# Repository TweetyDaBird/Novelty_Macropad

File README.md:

# Novelty_Macropad
 F*ckYou Macropad with 10 keys (ISO Enter, 2.75u Space, 7 pcs 1u + 1 pcs 1u/1.25u Shift)
 
 Inspired by this Reddit thread https://www.reddit.com/r/MechanicalKeyboards/comments/kn0asz/dont_let_your_memes_be_dreams/
 
 * Sub 100x100mm PCB for low cost fabrication
 * Easily soldereable for novice with simple components
 * 10 Cherry MX compatible Kaihl Hot-Swap sockets (with alternate 1u/1.25u layout for shift key)
 * Supports platemounted Cherry style stabilizers
 * Can be used with a ProMicro/EliteC connected to pinheader, or by soldering onboard SMD Atmega32u4 and associated components
 * If used with SMD components, USB-C port (USB2.0)
 * Includes .STEP file of PCB and plate holes for case design
 
 If anyone designs a nice design for a CNC machined or 3D printed case, please let me know (pull), and I'll include the files in the Github.

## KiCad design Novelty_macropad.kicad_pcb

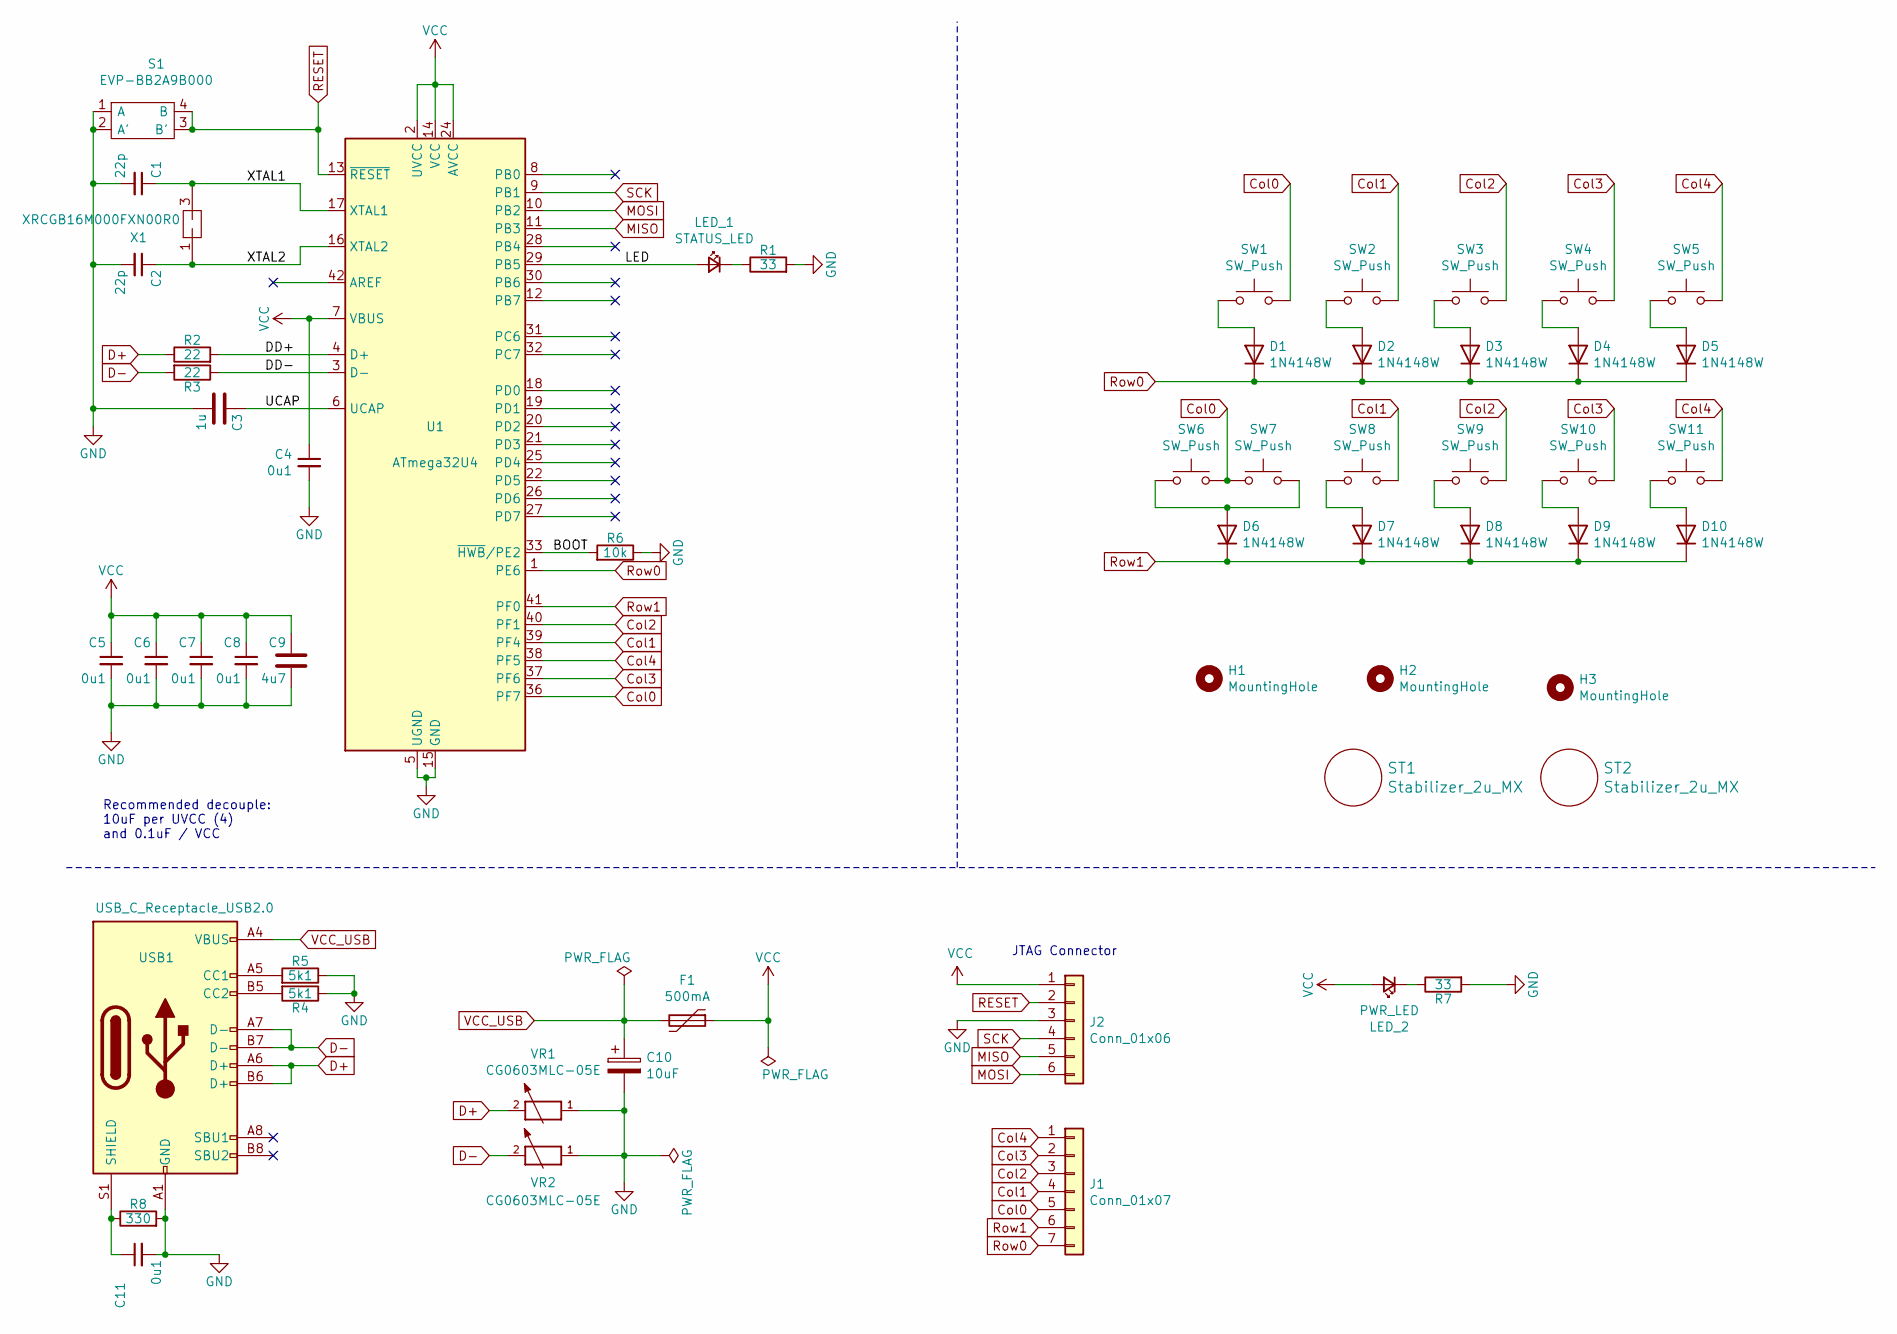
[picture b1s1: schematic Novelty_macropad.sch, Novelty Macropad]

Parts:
C1, C2: 22p; C_0603_1608Metric; Manufacturer_Part_Number 06035A220JAT2A; Mouser Part Number 581-06035A220J
C3: 1u; C_0805_2012Metric; Manufacturer_Part_Number CL21B105KBFNNNG; Mouser Part Number 187-CL21B105KBFNNNG
C4, C5, C6, C7, C8, C11: 0u1; C_0603_1608Metric; Manufacturer_Part_Number 06035C104JAT2A; Mouser Part Number 581-06035C104JAT2A
C9: 4u7; C_0805_2012Metric; Manufacturer_Part_Number C2012X7R1H475K125AC; Mouser Part Number 810-C2012X7R475K125C
C10: 10uF; CP_EIA-3216-18_Kemet-A; Manufacturer_Part_Number TAJA106M010RNJ; Mouser Part Number 581-TAJA106M010R
D1, D2, D3, D4, D5, D6, D7, D8, D9, D10: 1N4148W; Diode_DO35_SOD123
F1: 500mA; Fuse_0603_1608Metric; Manufacturer_Part_Number 04000025WR; Mouser Part Number 576-04000025WR
H1, H2, H3: MountingHole; MountingHole_2.7mm_M2.5
J1: Conn_01x07; PinHeader_1x07_P2.54mm_Vertical
J2: Conn_01x06; PinHeader_2x03_P2.54mm_Vertical; Manufacturer_Part_Number Pinheader
LED_1: STATUS_LED; LED_0603_1608Metric; Manufacturer_Part_Number APT1608EC; Mouser Part Number 604-APT1608EC
LED_2: PWR_LED; LED_0603_1608Metric; Manufacturer_Part_Number APT1608EC; Mouser Part Number 604-APT1608EC
R1, R7: 33; R_0603_1608Metric; Manufacturer_Part_Number ERJ-3EKF33R0V; Mouser Part Number 667-ERJ-3EKF33R0V
R2, R3: 22; R_0603_1608Metric; Manufacturer_Part_Number ERJ-3GEYJ220V; Mouser Part Number 667-ERJ-3GEYJ220V
R4, R5: 5k1; R_0603_1608Metric; Manufacturer_Part_Number ERJ-3EKF5101V; Mouser Part Number 667-ERJ-3EKF5101V
R6: 10k; R_0603_1608Metric; Manufacturer_Part_Number ERJ-3EKF1002V; Mouser Part Number 667-ERJ-3GEYJ103V
R8: 330; R_0603_1608Metric; Manufacturer_Part_Number ERJ-3EKF3300V; Mouser Part Number 667-ERJ-3EKF3300V
S1: EVP-BB2A9B000; EVPBB2A9B000; Mouser Part Number 667-EVP-BB2A9B000
ST1, ST2: Stabilizer_2u_MX; Stabilizer_MX_2u
SW1, SW2, SW3, SW4, SW5, SW6, SW7, SW8, SW9, SW10, SW11: SW_Push; Kailh_socket_MX
U1: ATmega32U4; QFN-44-1EP_7x7mm_P0.5mm_EP5.15x5.15mm_ThermalVias; Manufacturer_Part_Number ATMEGA32U4RC-MU; Mouser Part Number 556-ATMEGA32U4RC-MU
USB1: USB_C_Receptacle_USB2.0; HRO-TYPE-C-31-M-12-Assembly; Manufacturer_Part_Number HRO-TYPE-C-31-M-14
VR1, VR2: CG0603MLC-05E; R_0603_1608Metric; Mouser Part Number 652-CG0603MLC-05E
X1: XRCGB16M000FXN00R0; XRCGB16M000FXN1R0; Mouser Part Number 81-XRCGB16M000FXN00R

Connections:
/BOOT: R6.2, U1.33 (~HWB~/PE2)
/DD+: R2.2, U1.4 (D+)
/DD-: R3.1, U1.3 (D-)
/LED: LED_1.2 (A), U1.29 (PB5)
/UCAP: C3.1, U1.6 (UCAP)
/XTAL1: C1.1, U1.17 (XTAL1), X1.3
/XTAL2: C2.1, U1.16 (XTAL2), X1.1
Col0: J1.5, SW1.1, SW6.1, SW7.1, U1.36 (PF7)
Col1: J1.4, SW2.1, SW8.1, U1.39 (PF4)
Col2: J1.3, SW3.1, SW9.1, U1.40 (PF1)
Col3: J1.2, SW4.1, SW10.1, U1.37 (PF6)
Col4: J1.1, SW5.1, SW11.1, U1.38 (PF5)
D+: R2.1, USB1.A6 (D+), USB1.B6 (D+), VR1.2
D-: R3.2, USB1.A7 (D-), USB1.B7 (D-), VR2.2
GND: C1.2, C2.2, C3.2, C4.2, C5.2, C6.2, C7.2, C8.2, C9.2, C10.2, C11.2, J2.3, R1.2, R4.1, R5.1, R6.1, R7.2, R8.2, S1.1 (A), S1.2 (A'), U1.5 (UGND), U1.15 (GND), U1.23 (GND), U1.35 (GND), U1.43 (GND), USB1.A1 (GND), USB1.A12 (GND), USB1.B1 (GND), USB1.B12 (GND), VR1.1, VR2.1
MISO: J2.5, U1.11 (PB3)
MOSI: J2.6, U1.10 (PB2)
unnamed: C11.1, R8.1, USB1.S1 (SHIELD)
unnamed: D1.2 (A), SW1.2
unnamed: D2.2 (A), SW2.2
unnamed: D3.2 (A), SW3.2
unnamed: D4.2 (A), SW4.2
unnamed: D5.2 (A), SW5.2
unnamed: D6.2 (A), SW6.2, SW7.2
unnamed: D7.2 (A), SW8.2
unnamed: D8.2 (A), SW9.2
unnamed: D9.2 (A), SW10.2
unnamed: D10.2 (A), SW11.2
unnamed: LED_1.1 (K), R1.1
unnamed: LED_2.1 (K), R7.1
unnamed: R4.2, USB1.B5 (CC2)
unnamed: R5.2, USB1.A5 (CC1)
RESET: J2.2, S1.3 (B'), S1.4 (B), U1.13 (~RESET)
Row0: D1.1 (K), D2.1 (K), D3.1 (K), D4.1 (K), D5.1 (K), J1.7, U1.1 (PE6)
Row1: D6.1 (K), D7.1 (K), D8.1 (K), D9.1 (K), D10.1 (K), J1.6, U1.41 (PF0)
SCK: J2.4, U1.9 (PB1)
VCC: C4.1, C5.1, C6.1, C7.1, C8.1, C9.1, F1.1, J2.1, LED_2.2 (A), U1.2 (UVCC), U1.7 (VBUS), U1.14 (VCC), U1.24 (AVCC), U1.34 (VCC), U1.44 (AVCC)
VCC_USB: C10.1, F1.2, USB1.A4 (VBUS), USB1.A9 (VBUS), USB1.B4 (VBUS), USB1.B9 (VBUS)

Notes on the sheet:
Recommended decouple: 10uF per UVCC (4) and 0.1uF / VCC
JTAG Connector

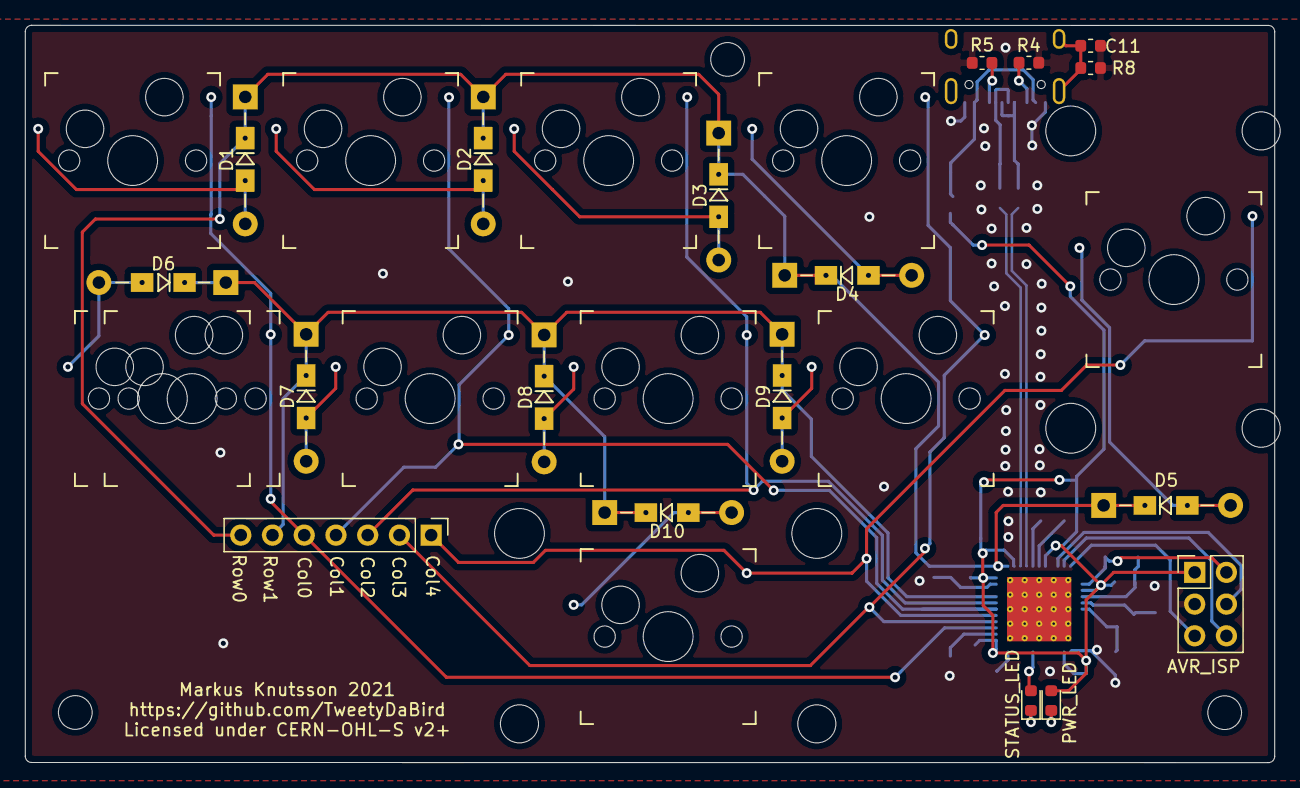
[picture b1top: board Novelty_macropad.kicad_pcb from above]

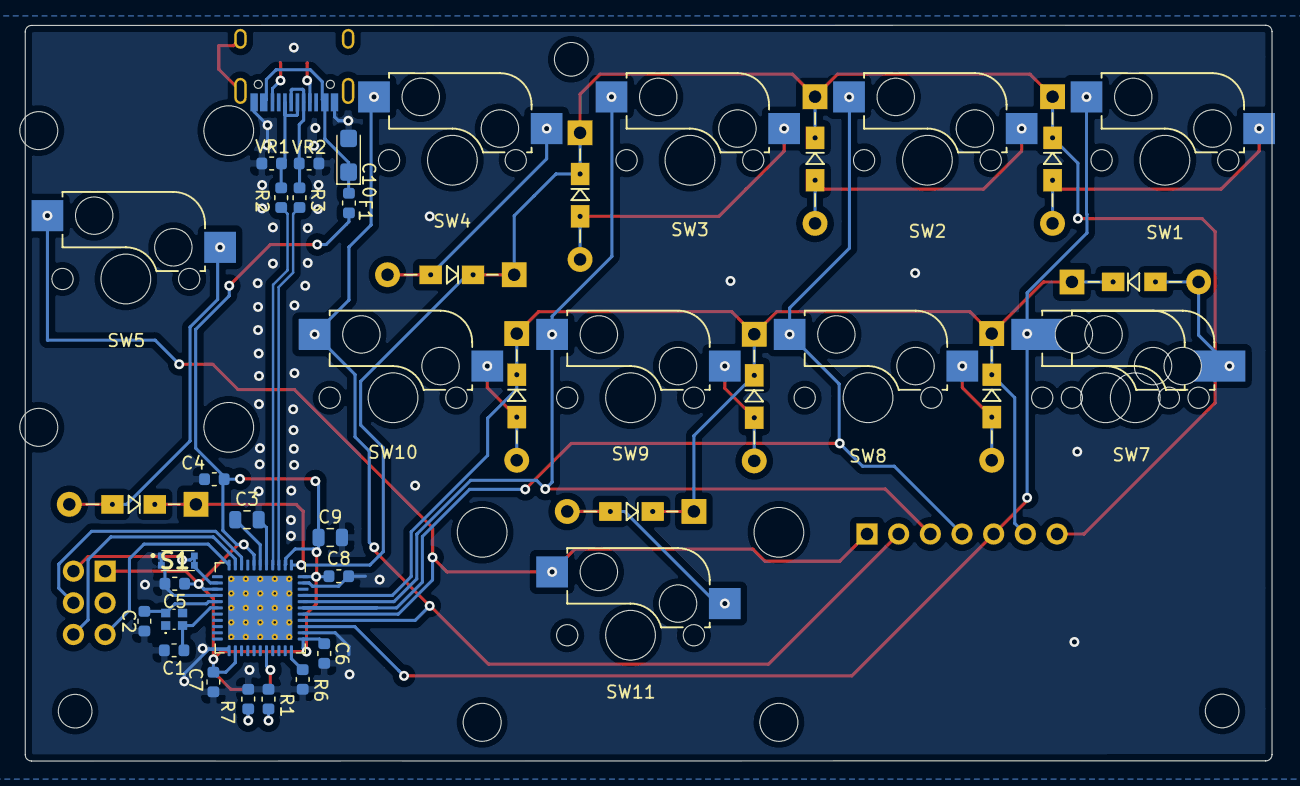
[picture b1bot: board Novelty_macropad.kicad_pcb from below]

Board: 2 copper layers, 100.0 x 59.0 mm, 56 parts (22 on the bottom side), 38 nets.

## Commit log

2021-01-01 initial design
2021-01-01 plate added, step files
2021-01-02 Corrected silkscreen and markings
2021-01-02 Added Licence files

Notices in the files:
Novelty_macropad.kicad_pcb:
Licensed under CERN-OHL-S v2 or superseding version
